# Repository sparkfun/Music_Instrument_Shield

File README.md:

SparkFun Music Instrument Shield
========================================

[*SparkFun Music Instrument Shield (DEV-10587)*](https://www.sparkfun.com/products/10587)

The SparkFun Musical Instrument Shield is an easy way to add great sounding MIDI sound to your next Arduino project. 
This board is built around the VS1053 MP3 and MIDI codec IC, wired in MIDI mode. 
Simply connect a speaker/stereo/pair of headphones to the 1/8" stereo jack on the shield and pass the proper serial commands to the IC and you’ll be playing music in no time!

Repository Contents
-------------------

* **/Firmware** - Example code 
* **/Hardware** - Eagle design files (.brd, .sch)
* **/Production** - Production panel files (.brd)

Documentation
--------------
* **[Hookup Guide](https://www.sparkfun.com/tutorials/302)** - Basic hookup guide for the Music Instrument Shield.
* **[SparkFun Fritzing repo](https://github.com/sparkfun/Fritzing_Parts)** - Fritzing diagrams for SparkFun products.
* **[SparkFun 3D Model repo](https://github.com/sparkfun/3D_Models)** - 3D models of SparkFun products. 

License Information
-------------------
This product is _**open source**_! 

The **hardware** is released under [Creative Commons ShareAlike 4.0 International](https://creativecommons.org/licenses/by-sa/4.0/).

The **code** is beerware; if you see me (or any other SparkFun employee) at the local, and you've found our code helpful, please buy us a round!

Please use, reuse, and modify these files as you see fit. Please maintain attribution to SparkFun Electronics and release anything derivative under the same license.

Distributed as-is; no warranty is given.

- Your friends at SparkFun.

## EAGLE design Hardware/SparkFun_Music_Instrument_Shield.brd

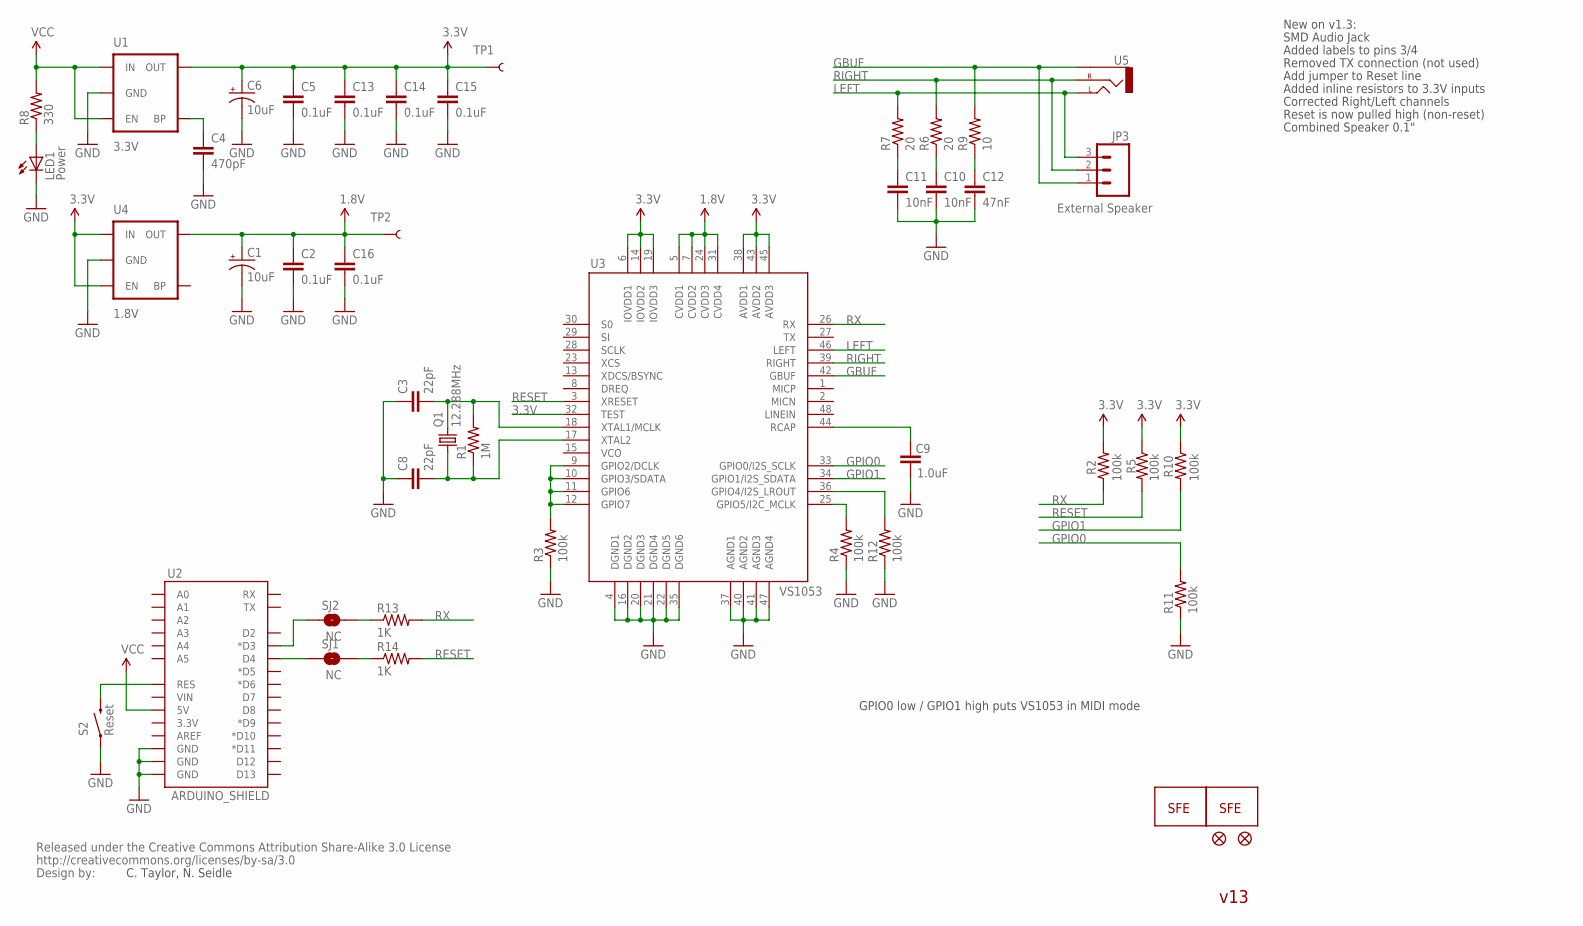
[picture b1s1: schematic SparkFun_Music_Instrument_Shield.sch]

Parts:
C1, C6: 10uF; EIA3216
C2, C5, C13, C14, C15, C16: 0.1uF; 0402-CAP
C3, C8: 22pF; 0402-CAP
C4: 470pF; 0402-CAP
C9: 1.0uF; 0402-CAP
C10, C11: 10nF; 0402-CAP
C12: 47nF; 0402-CAP
JP3: External Speaker; 1X03
LED1: Power; LED-0603
Q1: 12.288MHz; CRYSTAL-SMD-5X3
R1: 1M; 0402-RES
R2, R3, R4, R5, R10, R11, R12: 100k; 0402-RES
R6, R7: 20; 0402-RES
R8: 330; 0402-RES
R9: 10; 0402-RES
R13, R14: 1K; 0402-RES
S2: Reset; TACTILE_SWITCH_SMD
SJ1, SJ2: NC; SJ_2S-TRACE
TP1, TP2: TEST-POINT3X5; PAD.03X.05
U1: 3.3V; SOT23-5
U2: ARDUINO_SHIELD; DUEMILANOVE_SHIELD
U3: VS1053; LQFP-48
U4: 1.8V; SC70
U5: AUDIO-JACKSMD2; AUDIO-JACK-3.5MM-SMD
U$3: CREATIVE_COMMONS
U$4, U$5: FIDUCIAL1X2; FIDUCIAL-1X2
U$7, U$8: LOGO-SFENEW; SFE-NEW-WEBLOGO

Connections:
1.8V: C1.A (+), C2.1, C16.1, TP2.P$1, U3.5 (CVDD1), U3.7 (CVDD2), U3.24 (CVDD3), U3.31 (CVDD4), U4.5 (OUT)
3.3V: C5.1, C6.A (+), C13.1, C14.1, C15.1, R2.2, R5.1, R10.1, TP1.P$1, U1.5 (OUT), U3.6 (IOVDD1), U3.14 (IOVDD2), U3.19 (IOVDD3), U3.32 (TEST), U3.38 (AVDD1), U3.43 (AVDD2), U3.45 (AVDD3), U4.1 (IN), U4.3 (EN)
ARST: S2.3 (2), U2.RES
G1: R3.2, U3.9 (GPIO2/DCLK), U3.10 (GPIO3/SDATA), U3.11 (GPIO6), U3.12 (GPIO7)
G2: R4.2, U3.25 (GPIO5/I2C_MCLK)
GBUF: JP3.1, R9.2, U3.42 (GBUF), U5.SLEEVE
GND: C1.C (-), C2.2, C3.1, C4.2, C5.2, C6.C (-), C8.1, C9.1, C10.2, C11.2, C12.2, C13.2, C14.2, C15.2, C16.2, LED1.C, R3.1, R4.1, R11.1, R12.1, S2.1, U1.2 (GND), U2.GND@0 (GND), U2.GND@1 (GND), U2.GND@2 (GND), U3.4 (DGND1), U3.16 (DGND2), U3.20 (DGND3), U3.21 (DGND4), U3.22 (DGND5), U3.35 (DGND6), U3.37 (AGND1), U3.40 (AGND2), U3.41 (AGND3), U3.47 (AGND4), U4.2 (GND)
GPIO0: R11.2, U3.33 (GPIO0/I2S_SCLK)
GPIO1: R10.2, U3.34 (GPIO1/I2S_SDATA)
LEFT: JP3.3, R7.2, U3.46 (LEFT), U5.TIP (LEFT)
unnamed: C9.2, U3.44 (RCAP)
unnamed: C12.1, R9.1
unnamed: C10.1, R6.1
unnamed: C11.1, R7.1
unnamed: LED1.A, R8.1
unnamed: SJ1.1, U2.D4
unnamed: R13.1, SJ2.2
unnamed: C3.2, Q1.3 (2), R1.2, U3.18 (XTAL1/MCLK)
unnamed: C8.2, Q1.1, R1.1, U3.17 (XTAL2)
unnamed: R14.1, SJ1.2
unnamed: SJ2.1, U2.D3 (*D3)
unnamed: C4.1, U1.4 (BP)
unnamed: R12.2, U3.36 (GPIO4/I2S_LROUT)
RESET: R5.2, R14.2, U3.3 (XRESET)
RIGHT: JP3.2, R6.2, U3.39 (RIGHT), U5.RING (RIGHT)
RX: R2.1, R13.2, U3.26 (RX)
VCC: R8.2, U1.1 (IN), U1.3 (EN), U2.5V

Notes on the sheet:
GPIO0 low / GPIO1 high puts VS1053 in MIDI mode
C. Taylor, N. Seidle
New on v1.3:
SMD Audio Jack
Added labels to pins 3/4
Removed TX connection (not used)
Add jumper to Reset line
Added inline resistors to 3.3V inputs
Corrected Right/Left channels
Reset is now pulled high (non-reset)
Combined Speaker 0.1"
v13

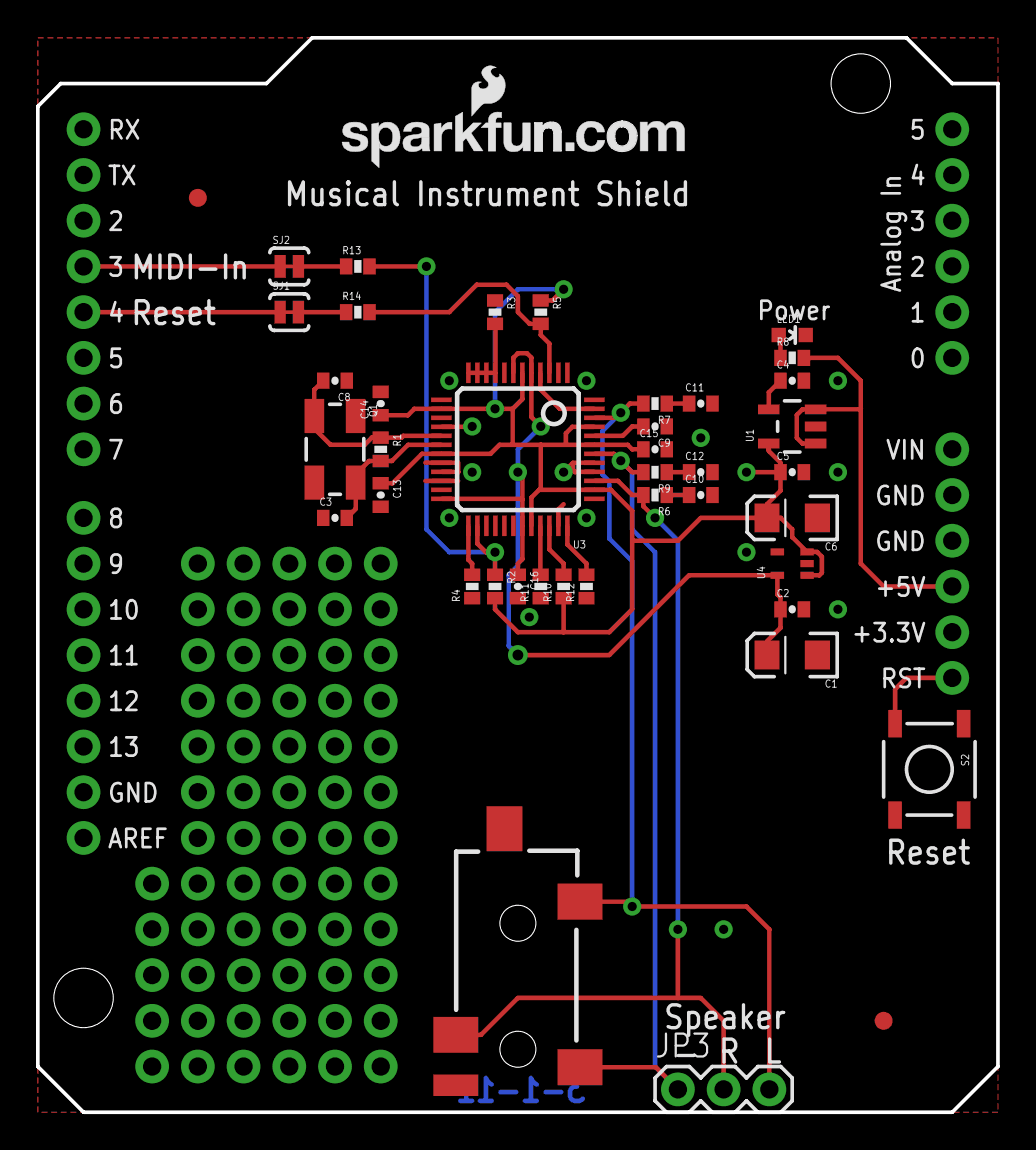
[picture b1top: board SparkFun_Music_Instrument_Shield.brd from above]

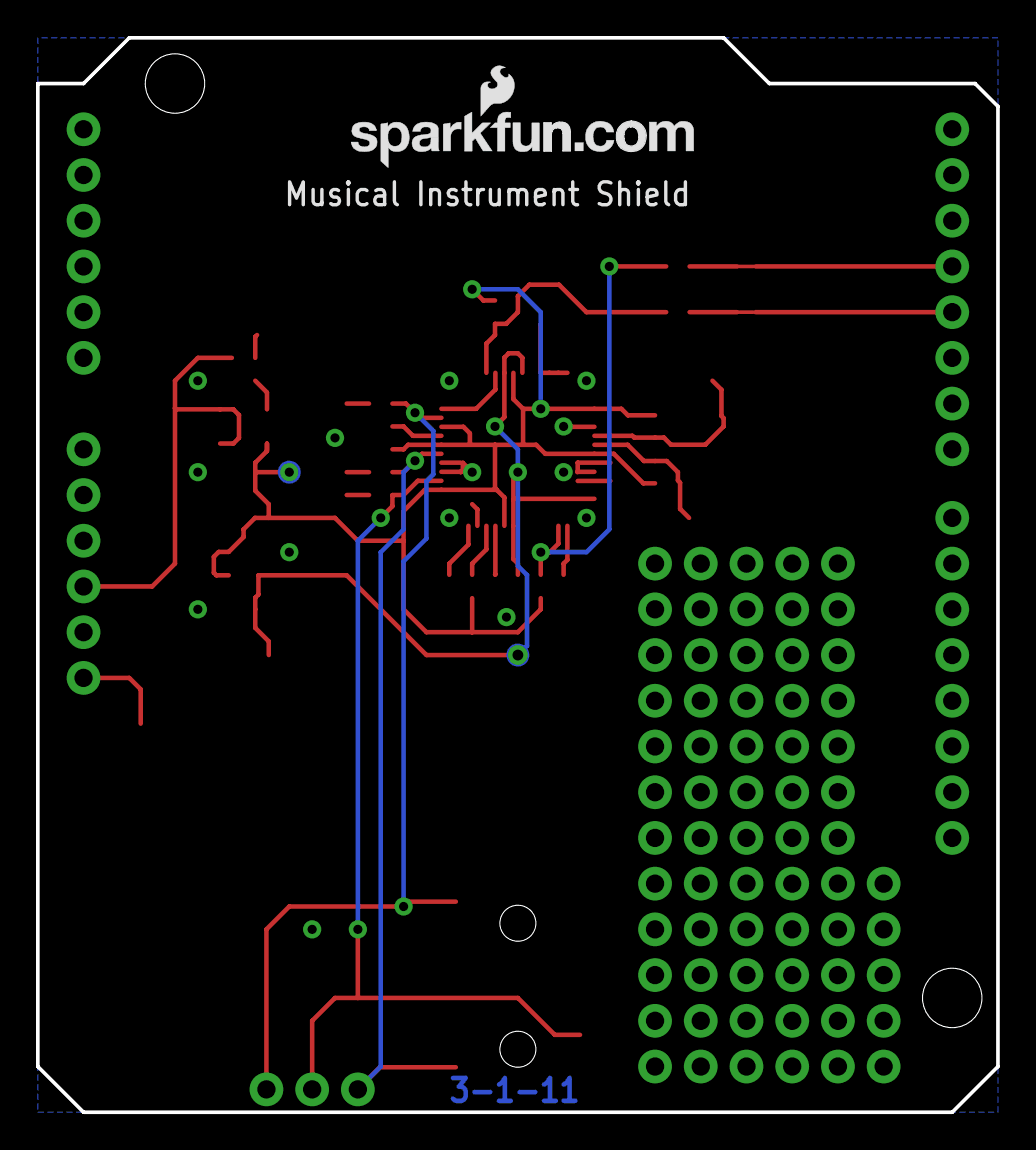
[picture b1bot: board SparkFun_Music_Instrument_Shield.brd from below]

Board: 2 copper layers, 53.3 x 59.7 mm, 47 parts (3 on the bottom side), 27 nets.

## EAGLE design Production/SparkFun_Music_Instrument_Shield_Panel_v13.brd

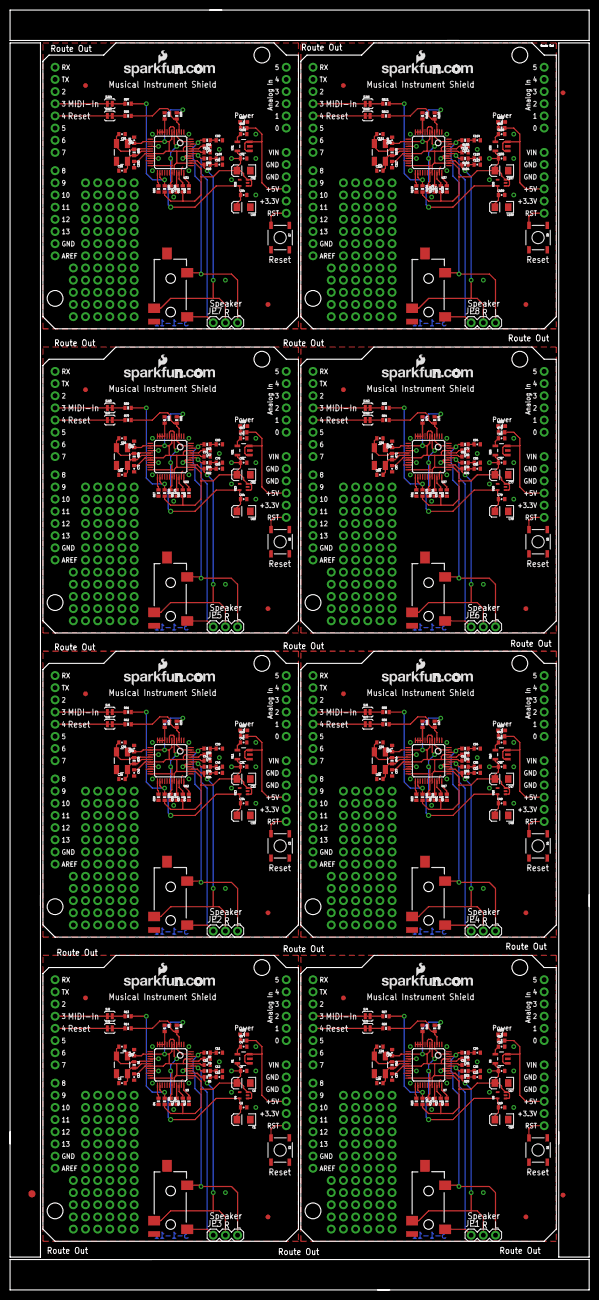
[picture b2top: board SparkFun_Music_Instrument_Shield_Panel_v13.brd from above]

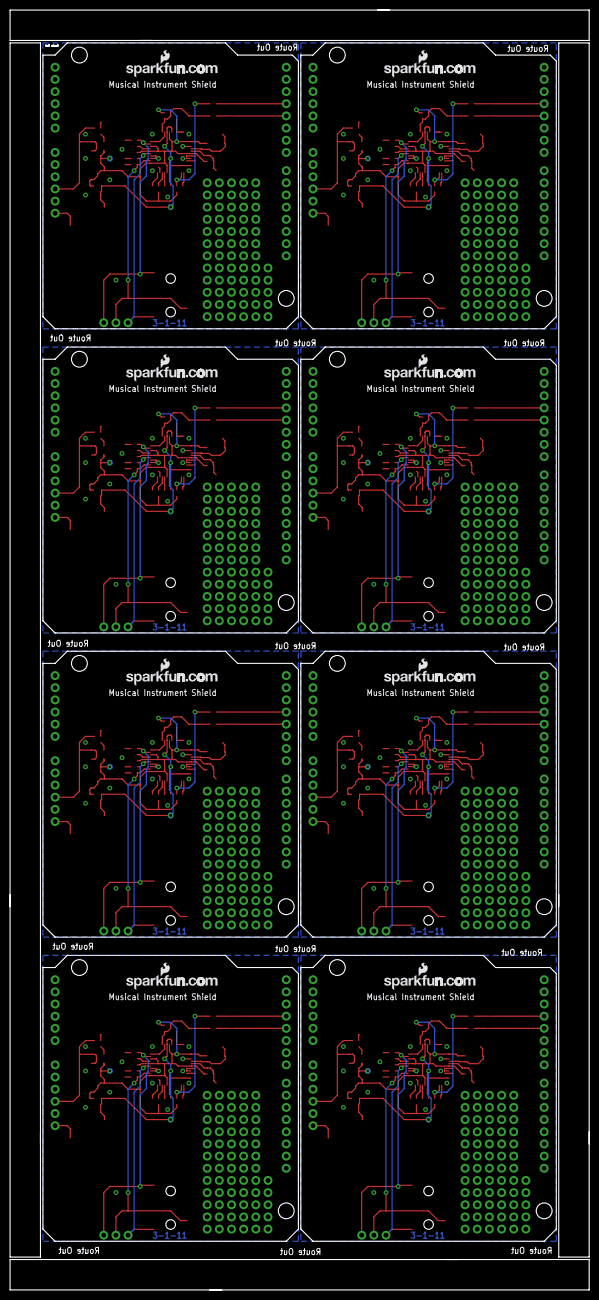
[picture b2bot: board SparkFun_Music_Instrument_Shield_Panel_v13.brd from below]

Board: 2 copper layers, 120.9 x 267.2 mm, 371 parts (24 on the bottom side), 216 nets.

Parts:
C1, C6, C17, C18, C32, C33, C47, C48, C62, C63, C77, C78, C92, C93, C107, C108: 10uF; EIA3216
C2, C5, C7, C13, C14, C15, C16, C19, C27, C28, C29, C30, C31, C34, C42, C43, C44, C45, C46, C49, C57, C58, C59, C60, C61, C64, C72, C73, C74, C75, C76, C79, C87, C88, C89, C90, C91, C94, C102, C103, C104, C105, C106, C109, C117, C118, C119, C120: 0.1uF; 0402-CAP
C3, C8, C20, C21, C35, C36, C50, C51, C65, C66, C80, C81, C95, C96, C110, C111: 22pF; 0402-CAP
C4, C26, C41, C56, C71, C86, C101, C116: 470pF; 0402-CAP
C9, C22, C37, C52, C67, C82, C97, C112: 1.0uF; 0402-CAP
C10, C11, C23, C24, C38, C39, C53, C54, C68, C69, C83, C84, C98, C99, C113, C114: 10nF; 0402-CAP
C12, C25, C40, C55, C70, C85, C100, C115: 47nF; 0402-CAP
E$1: FIDUCIAL-1.5X3
E$5, E$6: FIDUCIAL-1X2
JP1, JP2, JP3, JP4, JP5, JP6, JP7, JP8: External Speaker; 1X03
LED1, LED2, LED3, LED4, LED5, LED6, LED7, LED8: Power; LED-0603
Q1, Q2, Q3, Q4, Q5, Q6, Q7, Q8: 12.288MHz; CRYSTAL-SMD-5X3
R1, R16, R30, R44, R58, R72, R86, R100: 1M; 0402-RES
R2, R3, R4, R5, R10, R11, R12, R17, R18, R19, R23, R24, R25, R26, R31, R32, R33, R37, R38, R39, R40, R45, R46, R47, R51, R52, R53, R54, R59, R60, R61, R65, R66, R67, R68, R73, R74, R75, R79, R80, R81, R82, R87, R88, R89, R93, R94, R95, R96, R101, R102, R103, R107, R108, R109, R110: 100k; 0402-RES
R6, R7, R20, R21, R34, R35, R48, R49, R62, R63, R76, R77, R90, R91, R104, R105: 20; 0402-RES
R8, R15, R29, R43, R57, R71, R85, R99: 330; 0402-RES
R9, R22, R36, R50, R64, R78, R92, R106: 10; 0402-RES
R13, R14, R27, R28, R41, R42, R55, R56, R69, R70, R83, R84, R97, R98, R111, R112: 1K; 0402-RES
S1, S2, S3, S4, S5, S6, S7, S8: Reset; TACTILE_SWITCH_SMD
SJ1, SJ2, SJ3, SJ4, SJ5, SJ6, SJ7, SJ8, SJ9, SJ10, SJ11, SJ12, SJ13, SJ14, SJ15, SJ16: NC; SJ_2S-TRACE
TP1, TP2, TP3, TP4, TP5, TP6, TP7, TP8, TP9, TP10, TP11, TP12, TP13, TP14, TP15, TP16: PAD.03X.05
U1, U6, U11, U16, U21, U26, U31, U36: 3.3V; SOT23-5
U2, U9, U14, U19, U24, U29, U34, U39: ARDUINO_SHIELD; DUEMILANOVE_SHIELD
U3, U7, U12, U17, U22, U27, U32, U37: VS1053; LQFP-48
U4, U8, U13, U18, U23, U28, U33, U38: 1.8V; SC70
U5, U10, U15, U20, U25, U30, U35, U40: AUDIO-JACK-3.5MM-SMD
U$1, U$6, U$7, U$8, U$9, U$12, U$13, U$16, U$17, U$20, U$21, U$24, U$25, U$28, U$29, U$32: LOGO-SFENEW; SFE-NEW-WEBLOGO
U$2, U$3, U$4, U$5, U$10, U$11, U$14, U$15, U$18, U$19, U$22, U$23, U$26, U$27, U$30, U$31: FIDUCIAL1X2; FIDUCIAL-1X2

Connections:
1.8V: C1.A, C2.1, C16.1, TP2.P$1, U3.5, U3.7, U3.24, U3.31, U4.5
1.8V1: C18.A, C19.1, C30.1, TP4.P$1, U7.5, U7.7, U7.24, U7.31, U8.5
1.8V2: C33.A, C34.1, C45.1, TP6.P$1, U12.5, U12.7, U12.24, U12.31, U13.5
1.8V3: C48.A, C49.1, C60.1, TP8.P$1, U17.5, U17.7, U17.24, U17.31, U18.5
1.8V4: C63.A, C64.1, C75.1, TP10.P$1, U22.5, U22.7, U22.24, U22.31, U23.5
1.8V5: C78.A, C79.1, C90.1, TP12.P$1, U27.5, U27.7, U27.24, U27.31, U28.5
1.8V6: C93.A, C94.1, C105.1, TP14.P$1, U32.5, U32.7, U32.24, U32.31, U33.5
1.8V7: C108.A, C109.1, C120.1, TP16.P$1, U37.5, U37.7, U37.24, U37.31, U38.5
3.3V: C5.1, C6.A, C13.1, C14.1, C15.1, R2.2, R5.1, R10.1, TP1.P$1, U1.5, U3.6, U3.14, U3.19, U3.32, U3.38, U3.43, U3.45, U4.1, U4.3
3.3V1: C7.1, C17.A, C27.1, C28.1, C29.1, R17.2, R19.1, R23.1, TP3.P$1, U6.5, U7.6, U7.14, U7.19, U7.32, U7.38, U7.43, U7.45, U8.1, U8.3
3.3V2: C31.1, C32.A, C42.1, C43.1, C44.1, R31.2, R33.1, R37.1, TP5.P$1, U11.5, U12.6, U12.14, U12.19, U12.32, U12.38, U12.43, U12.45, U13.1, U13.3
3.3V3: C46.1, C47.A, C57.1, C58.1, C59.1, R45.2, R47.1, R51.1, TP7.P$1, U16.5, U17.6, U17.14, U17.19, U17.32, U17.38, U17.43, U17.45, U18.1, U18.3
3.3V4: C61.1, C62.A, C72.1, C73.1, C74.1, R59.2, R61.1, R65.1, TP9.P$1, U21.5, U22.6, U22.14, U22.19, U22.32, U22.38, U22.43, U22.45, U23.1, U23.3
3.3V5: C76.1, C77.A, C87.1, C88.1, C89.1, R73.2, R75.1, R79.1, TP11.P$1, U26.5, U27.6, U27.14, U27.19, U27.32, U27.38, U27.43, U27.45, U28.1, U28.3
3.3V6: C91.1, C92.A, C102.1, C103.1, C104.1, R87.2, R89.1, R93.1, TP13.P$1, U31.5, U32.6, U32.14, U32.19, U32.32, U32.38, U32.43, U32.45, U33.1, U33.3
3.3V7: C106.1, C107.A, C117.1, C118.1, C119.1, R101.2, R103.1, R107.1, TP15.P$1, U36.5, U37.6, U37.14, U37.19, U37.32, U37.38, U37.43, U37.45, U38.1, U38.3
ARST: S2.3, U2.RES
ARST1: S1.3, U9.RES
ARST2: S3.3, U14.RES
ARST3: S4.3, U19.RES
ARST4: S5.3, U24.RES
ARST5: S6.3, U29.RES
ARST6: S7.3, U34.RES
ARST7: S8.3, U39.RES
G1: R3.2, U3.9, U3.10, U3.11, U3.12
G2: R4.2, U3.25
G3: R18.2, U7.9, U7.10, U7.11, U7.12
G4: R25.2, U7.25
G5: R32.2, U12.9, U12.10, U12.11, U12.12
G6: R39.2, U12.25
G7: R46.2, U17.9, U17.10, U17.11, U17.12
G8: R53.2, U17.25
G9: R60.2, U22.9, U22.10, U22.11, U22.12
G10: R67.2, U22.25
G11: R74.2, U27.9, U27.10, U27.11, U27.12
G12: R81.2, U27.25
G13: R88.2, U32.9, U32.10, U32.11, U32.12
G14: R95.2, U32.25
G15: R102.2, U37.9, U37.10, U37.11, U37.12
G16: R109.2, U37.25
GBUF: JP3.1, R9.2, U3.42, U5.SLEEVE
GBUF1: JP1.1, R22.2, U7.42, U10.SLEEVE
GBUF2: JP2.1, R36.2, U12.42, U15.SLEEVE
GBUF3: JP4.1, R50.2, U17.42, U20.SLEEVE
GBUF4: JP5.1, R64.2, U22.42, U25.SLEEVE
GBUF5: JP6.1, R78.2, U27.42, U30.SLEEVE
GBUF6: JP7.1, R92.2, U32.42, U35.SLEEVE
GBUF7: JP8.1, R106.2, U37.42, U40.SLEEVE
GND: C1.C, C2.2, C3.1, C4.2, C5.2, C6.C, C8.1, C9.1, C10.2, C11.2, C12.2, C13.2, C14.2, C15.2, C16.2, LED1.C, R3.1, R4.1, R11.1, R12.1, S2.1, U1.2, U2.GND@0, U2.GND@1, U2.GND@2, U3.4, U3.16, U3.20, U3.21, U3.22, U3.35, U3.37, U3.40, U3.41, U3.47, U4.2
GND1: C7.2, C17.C, C18.C, C19.2, C20.1, C21.1, C22.1, C23.2, C24.2, C25.2, C26.2, C27.2, C28.2, C29.2, C30.2, LED2.C, R18.1, R24.1, R25.1, R26.1, S1.1, U6.2, U7.4, U7.16, U7.20, U7.21, U7.22, U7.35, U7.37, U7.40, U7.41, U7.47, U8.2, U9.GND@0, U9.GND@1, U9.GND@2
GND2: C31.2, C32.C, C33.C, C34.2, C35.1, C36.1, C37.1, C38.2, C39.2, C40.2, C41.2, C42.2, C43.2, C44.2, C45.2, LED3.C, R32.1, R38.1, R39.1, R40.1, S3.1, U11.2, U12.4, U12.16, U12.20, U12.21, U12.22, U12.35, U12.37, U12.40, U12.41, U12.47, U13.2, U14.GND@0, U14.GND@1, U14.GND@2
GND3: C46.2, C47.C, C48.C, C49.2, C50.1, C51.1, C52.1, C53.2, C54.2, C55.2, C56.2, C57.2, C58.2, C59.2, C60.2, LED4.C, R46.1, R52.1, R53.1, R54.1, S4.1, U16.2, U17.4, U17.16, U17.20, U17.21, U17.22, U17.35, U17.37, U17.40, U17.41, U17.47, U18.2, U19.GND@0, U19.GND@1, U19.GND@2
GND4: C61.2, C62.C, C63.C, C64.2, C65.1, C66.1, C67.1, C68.2, C69.2, C70.2, C71.2, C72.2, C73.2, C74.2, C75.2, LED5.C, R60.1, R66.1, R67.1, R68.1, S5.1, U21.2, U22.4, U22.16, U22.20, U22.21, U22.22, U22.35, U22.37, U22.40, U22.41, U22.47, U23.2, U24.GND@0, U24.GND@1, U24.GND@2
GND5: C76.2, C77.C, C78.C, C79.2, C80.1, C81.1, C82.1, C83.2, C84.2, C85.2, C86.2, C87.2, C88.2, C89.2, C90.2, LED6.C, R74.1, R80.1, R81.1, R82.1, S6.1, U26.2, U27.4, U27.16, U27.20, U27.21, U27.22, U27.35, U27.37, U27.40, U27.41, U27.47, U28.2, U29.GND@0, U29.GND@1, U29.GND@2
GND6: C91.2, C92.C, C93.C, C94.2, C95.1, C96.1, C97.1, C98.2, C99.2, C100.2, C101.2, C102.2, C103.2, C104.2, C105.2, LED7.C, R88.1, R94.1, R95.1, R96.1, S7.1, U31.2, U32.4, U32.16, U32.20, U32.21, U32.22, U32.35, U32.37, U32.40, U32.41, U32.47, U33.2, U34.GND@0, U34.GND@1, U34.GND@2
GND7: C106.2, C107.C, C108.C, C109.2, C110.1, C111.1, C112.1, C113.2, C114.2, C115.2, C116.2, C117.2, C118.2, C119.2, C120.2, LED8.C, R102.1, R108.1, R109.1, R110.1, S8.1, U36.2, U37.4, U37.16, U37.20, U37.21, U37.22, U37.35, U37.37, U37.40, U37.41, U37.47, U38.2, U39.GND@0, U39.GND@1, U39.GND@2
GPIO0: R11.2, U3.33
GPIO1: R10.2, U3.34
GPIO2: R24.2, U7.33
GPIO3: R23.2, U7.34
GPIO4: R38.2, U12.33
GPIO5: R37.2, U12.34
GPIO6: R52.2, U17.33
GPIO7: R51.2, U17.34
GPIO8: R66.2, U22.33
GPIO9: R65.2, U22.34
GPIO10: R80.2, U27.33
GPIO11: R79.2, U27.34
GPIO12: R94.2, U32.33
GPIO13: R93.2, U32.34
GPIO14: R108.2, U37.33
GPIO15: R107.2, U37.34
LEFT: JP3.3, R7.2, U3.46, U5.TIP
LEFT1: JP1.3, R21.2, U7.46, U10.TIP
LEFT2: JP2.3, R35.2, U12.46, U15.TIP
LEFT3: JP4.3, R49.2, U17.46, U20.TIP
LEFT4: JP5.3, R63.2, U22.46, U25.TIP
LEFT5: JP6.3, R77.2, U27.46, U30.TIP
LEFT6: JP7.3, R91.2, U32.46, U35.TIP
LEFT7: JP8.3, R105.2, U37.46, U40.TIP
unnamed: C9.2, U3.44
unnamed: C12.1, R9.1
unnamed: C10.1, R6.1
unnamed: C11.1, R7.1
unnamed: LED1.A, R8.1
unnamed: SJ1.1, U2.D4
unnamed: R13.1, SJ2.2
unnamed: C3.2, Q1.3, R1.2, U3.18
unnamed: C8.2, Q1.1, R1.1, U3.17
unnamed: R14.1, SJ1.2
unnamed: LED2.A, R15.1
unnamed: SJ2.1, U2.D3
unnamed: C20.2, Q2.3, R16.2, U7.18
unnamed: C21.2, Q2.1, R16.1, U7.17
unnamed: C22.2, U7.44
unnamed: C25.1, R22.1
unnamed: C24.1, R21.1
unnamed: C23.1, R20.1
unnamed: C4.1, U1.4
unnamed: R12.2, U3.36
unnamed: C26.1, U6.4
unnamed: R26.2, U7.36
unnamed: SJ3.1, U9.D4
unnamed: R28.1, SJ3.2
unnamed: SJ4.1, U9.D3
unnamed: R27.1, SJ4.2
unnamed: LED3.A, R29.1
unnamed: C35.2, Q3.3, R30.2, U12.18
unnamed: C36.2, Q3.1, R30.1, U12.17
unnamed: C37.2, U12.44
unnamed: C40.1, R36.1
unnamed: C39.1, R35.1
unnamed: C38.1, R34.1
unnamed: C41.1, U11.4
unnamed: R40.2, U12.36
unnamed: SJ5.1, U14.D4
unnamed: R42.1, SJ5.2
unnamed: SJ6.1, U14.D3
unnamed: R41.1, SJ6.2
unnamed: LED4.A, R43.1
unnamed: C50.2, Q4.3, R44.2, U17.18
unnamed: C51.2, Q4.1, R44.1, U17.17
unnamed: C52.2, U17.44
unnamed: C55.1, R50.1
unnamed: C54.1, R49.1
unnamed: C53.1, R48.1
unnamed: C56.1, U16.4
unnamed: R54.2, U17.36
unnamed: SJ7.1, U19.D4
unnamed: R56.1, SJ7.2
unnamed: SJ8.1, U19.D3
unnamed: R55.1, SJ8.2
unnamed: LED5.A, R57.1
unnamed: C65.2, Q5.3, R58.2, U22.18
unnamed: C66.2, Q5.1, R58.1, U22.17
unnamed: C67.2, U22.44
unnamed: C70.1, R64.1
unnamed: C69.1, R63.1
unnamed: C68.1, R62.1
unnamed: C71.1, U21.4
unnamed: R68.2, U22.36
unnamed: SJ9.1, U24.D4
unnamed: R70.1, SJ9.2
unnamed: SJ10.1, U24.D3
unnamed: R69.1, SJ10.2
unnamed: LED6.A, R71.1
unnamed: C80.2, Q6.3, R72.2, U27.18
unnamed: C81.2, Q6.1, R72.1, U27.17
unnamed: C82.2, U27.44
unnamed: C85.1, R78.1
unnamed: C84.1, R77.1
unnamed: C83.1, R76.1
unnamed: C86.1, U26.4
unnamed: R82.2, U27.36
unnamed: SJ11.1, U29.D4
unnamed: R84.1, SJ11.2
unnamed: SJ12.1, U29.D3
unnamed: R83.1, SJ12.2
unnamed: LED7.A, R85.1
unnamed: C95.2, Q7.3, R86.2, U32.18
unnamed: C96.2, Q7.1, R86.1, U32.17
unnamed: C97.2, U32.44
unnamed: C100.1, R92.1
unnamed: C99.1, R91.1
unnamed: C98.1, R90.1
unnamed: C101.1, U31.4
unnamed: R96.2, U32.36
unnamed: SJ13.1, U34.D4
unnamed: R98.1, SJ13.2
unnamed: SJ14.1, U34.D3
unnamed: R97.1, SJ14.2
unnamed: LED8.A, R99.1
unnamed: C110.2, Q8.3, R100.2, U37.18
unnamed: C111.2, Q8.1, R100.1, U37.17
unnamed: C112.2, U37.44
unnamed: C115.1, R106.1
unnamed: C114.1, R105.1
unnamed: C113.1, R104.1
unnamed: C116.1, U36.4
unnamed: R110.2, U37.36
unnamed: SJ15.1, U39.D4
unnamed: R112.1, SJ15.2
unnamed: SJ16.1, U39.D3
unnamed: R111.1, SJ16.2
RESET: R5.2, R14.2, U3.3
RESET1: R19.2, R28.2, U7.3
RESET2: R33.2, R42.2, U12.3
RESET3: R47.2, R56.2, U17.3
RESET4: R61.2, R70.2, U22.3
RESET5: R75.2, R84.2, U27.3
RESET6: R89.2, R98.2, U32.3
RESET7: R103.2, R112.2, U37.3
RIGHT: JP3.2, R6.2, U3.39, U5.RING
RIGHT1: JP1.2, R20.2, U7.39, U10.RING
RIGHT2: JP2.2, R34.2, U12.39, U15.RING
RIGHT3: JP4.2, R48.2, U17.39, U20.RING
RIGHT4: JP5.2, R62.2, U22.39, U25.RING
RIGHT5: JP6.2, R76.2, U27.39, U30.RING
RIGHT6: JP7.2, R90.2, U32.39, U35.RING
RIGHT7: JP8.2, R104.2, U37.39, U40.RING
RX: R2.1, R13.2, U3.26
RX1: R17.1, R27.2, U7.26
RX2: R31.1, R41.2, U12.26
RX3: R45.1, R55.2, U17.26
RX4: R59.1, R69.2, U22.26
RX5: R73.1, R83.2, U27.26
RX6: R87.1, R97.2, U32.26
RX7: R101.1, R111.2, U37.26
VCC: R8.2, U1.1, U1.3, U2.5V
VCC1: R15.2, U6.1, U6.3, U9.5V
VCC2: R29.2, U11.1, U11.3, U14.5V
VCC3: R43.2, U16.1, U16.3, U19.5V
VCC4: R57.2, U21.1, U21.3, U24.5V
VCC5: R71.2, U26.1, U26.3, U29.5V
VCC6: R85.2, U31.1, U31.3, U34.5V
VCC7: R99.2, U36.1, U36.3, U39.5V

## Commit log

2015-05-06 Adding hardware, demo sketch, readme links
2015-10-19 created panel v13
2023-08-20 Create SparkFun MIDI shield

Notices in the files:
parts and their libraries:
SparkFun: Released under the Creative Commons Attribution Share-Alike 3.0 License
SparkFun: http://creativecommons.org/licenses/by-sa/3.0
SparkFun-Aesthetics: Licensing: CC v3.0 Share-Alike You are welcome to use this library for commercial purposes.
